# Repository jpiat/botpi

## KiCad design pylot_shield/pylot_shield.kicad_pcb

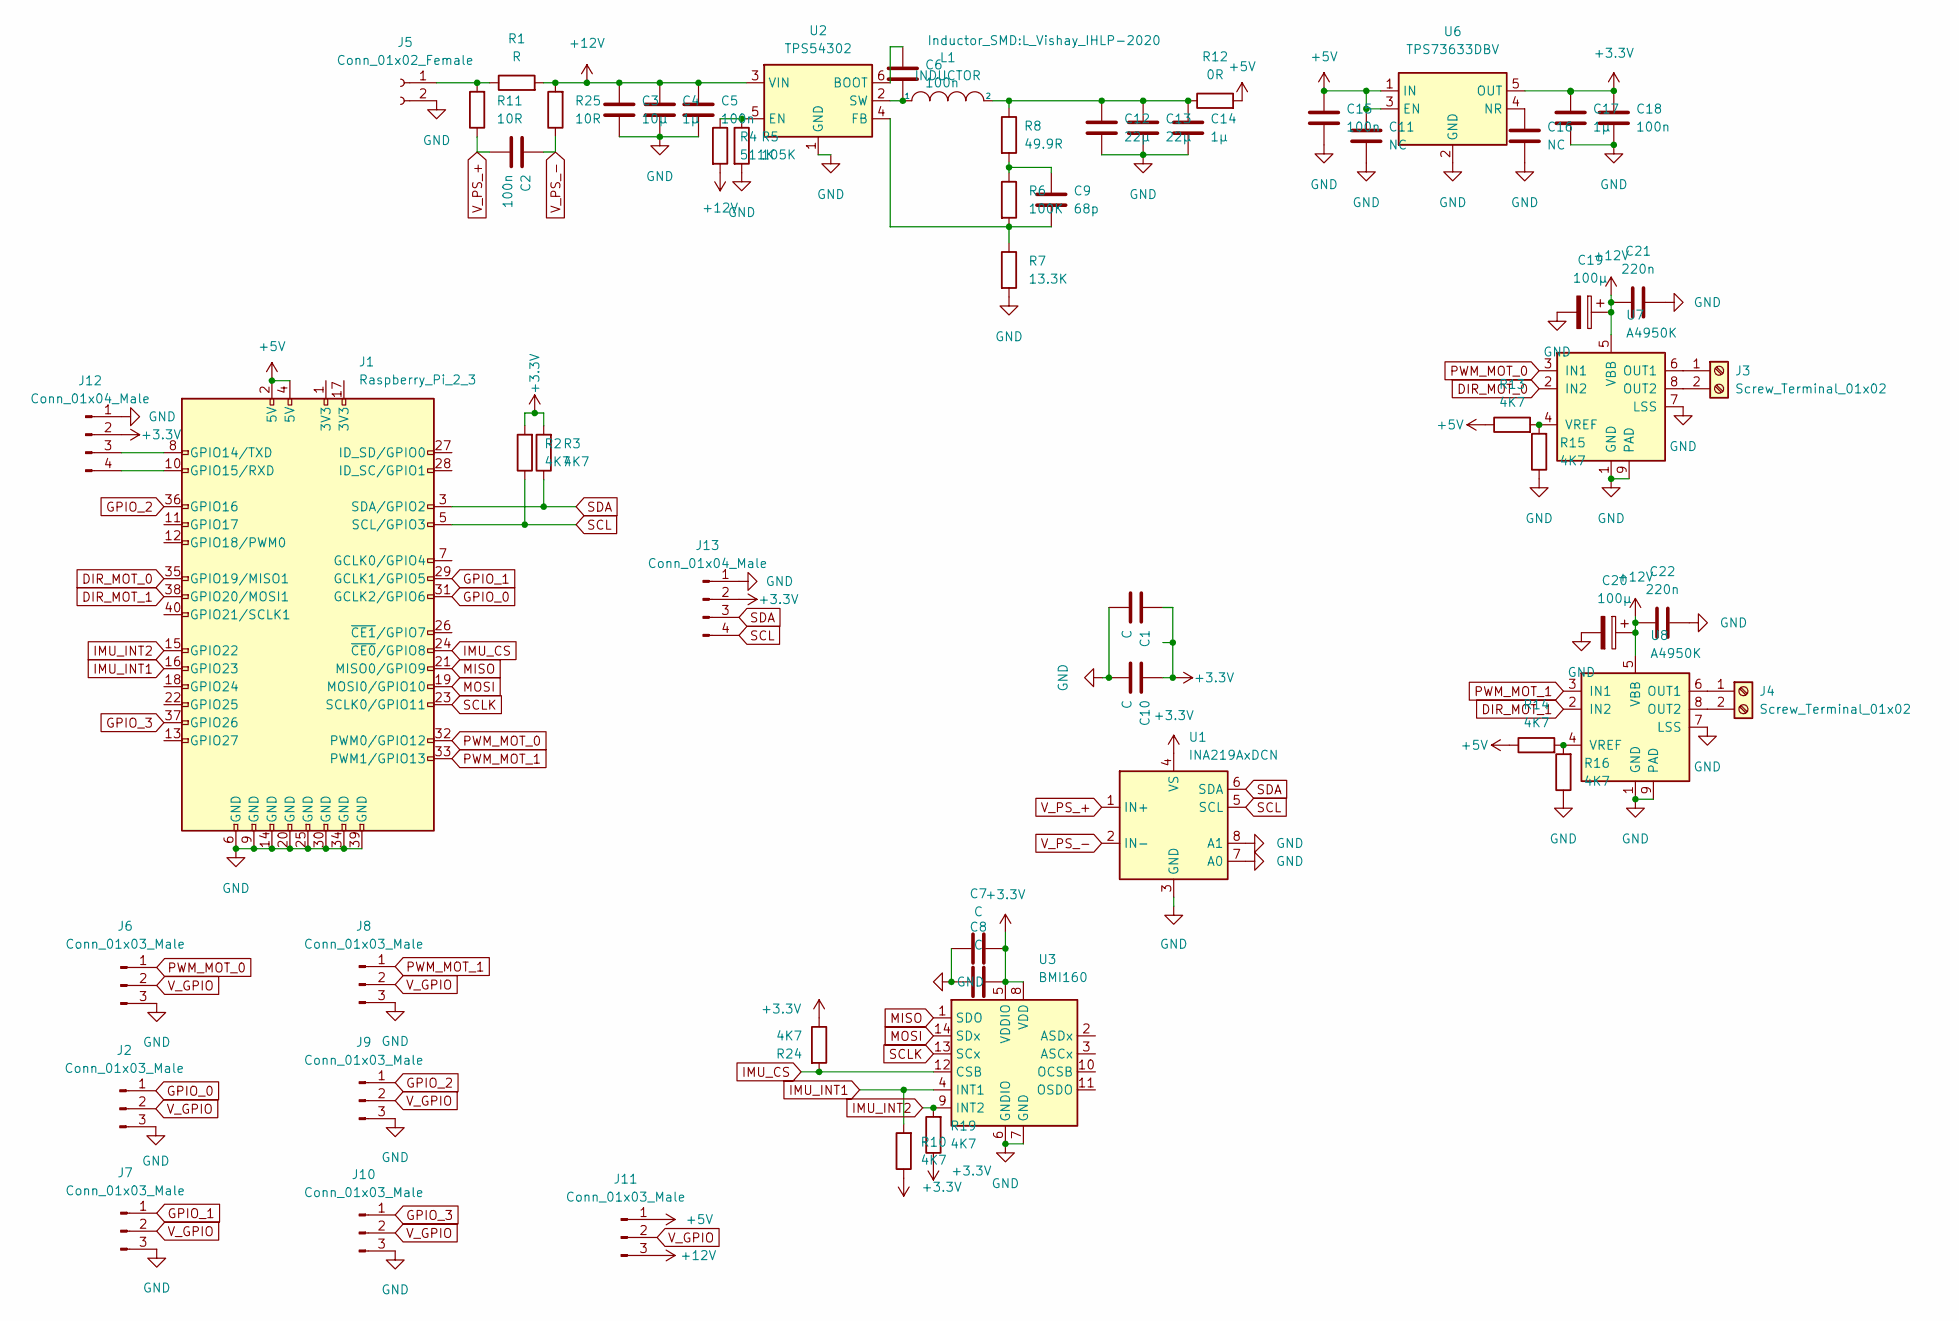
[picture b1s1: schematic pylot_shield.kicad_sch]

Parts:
C1, C7, C8, C10: C; C_0603_1608Metric
C2, C5, C6, C15, C18: 100n; C_0603_1608Metric
C3: 10µ; C_1206_3216Metric
C4: 1µ; C_1206_3216Metric
C9: 68p; C_0603_1608Metric
C11, C16: NC; C_0603_1608Metric
C12, C13: 22µ; C_1206_3216Metric
C14, C17: 1µ; C_0603_1608Metric
C19, C20: 100µ; CP_Radial_D6.3mm_P2.50mm
C21, C22: 220n; C_0603_1608Metric
J1: Raspberry_Pi_2_3; ADA3708_RPI-ZERO
J2, J6, J7, J8, J9, J10: Conn_01x03_Male; PinHeader_1x03_P2.54mm_Vertical
J3, J4: Screw_Terminal_01x02; TerminalBlock_Phoenix_PT-1,5-2-3.5-H_1x02_P3.50mm_Horizontal
J5: Conn_01x02_Female; XT30
J11: Conn_01x03_Male; SolderJumper-3_P1.3mm_Bridged2Bar12_RoundedPad1.0x1.5mm
J12, J13: Conn_01x04_Male; PinHeader_1x04_P2.00mm_Vertical
L1: INDUCTOR; L_Vishay_IHLP-2020
R1: R; R_2512_6332Metric
R2, R3, R10, R13, R14, R15, R16, R19, R24: 4K7; R_0603_1608Metric
R4: 511K; R_0603_1608Metric
R5: 105K; R_0603_1608Metric
R6: 100K; R_0603_1608Metric
R7: 13.3K; R_0603_1608Metric
R8: 49.9R; R_0603_1608Metric
R11, R25: 10R; R_0603_1608Metric
R12: 0R; R_0603_1608Metric
U1: INA219AxDCN; SOT-23-8
U2: TPS54302; SOT-23-6
U3: BMI160; Bosch_LGA-14_3x2.5mm_P0.5mm
U6: TPS73633DBV; SOT-23-5
U7, U8: A4950K; SOIC-8-1EP_3.9x4.9mm_P1.27mm_EP2.41x3.3mm

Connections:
+3.3V: C1.1, C7.2, C8.2, C10.1, C17.1, C18.1, J12.2, J13.2, R2.2, R3.2, R10.1, R19.1, R24.1, U1.4 (VS), U3.5 (VDDIO), U3.8 (VDD), U6.5 (OUT)
+5V: C11.1, C15.1, J1.2 (5V), J1.4 (5V), J11.1, R12.2, R13.1, R14.1, U6.1 (IN), U6.3 (EN)
+12V: C3.1, C4.1, C5.1, C19.1, C20.1, C21.1, C22.1, J11.3, R1.2, R4.2, R25.2, U2.3 (VIN), U7.5 (VBB), U8.5 (VBB)
DIR_MOT_0: J1.35 (GPIO19/MISO1), U7.2 (IN2)
DIR_MOT_1: J1.38 (GPIO20/MOSI1), U8.2 (IN2)
GND: C1.2, C3.2, C4.2, C5.2, C7.1, C8.1, C10.2, C11.2, C12.2, C13.2, C14.2, C15.2, C16.2, C17.2, C18.2, C19.2, C20.2, C21.2, C22.2, J1.6 (GND), J1.9 (GND), J1.14 (GND), J1.20 (GND), J1.25 (GND), J1.30 (GND), J1.34 (GND), J1.39 (GND), J2.3, J5.2, J6.3, J7.3, J8.3, J9.3, J10.3, J12.1, J13.1, R5.2, R7.2, R15.1, R16.1, U1.3 (GND), U1.7 (A0), U1.8 (A1), U2.1 (GND), U3.6 (GNDIO), U3.7 (GND), U6.2 (GND), U7.1 (GND), U7.7 (LSS), U7.9 (PAD), U8.1 (GND), U8.7 (LSS), U8.9 (PAD)
GPIO_0: J1.31 (GCLK2/GPIO6), J2.1
GPIO_1: J1.29 (GCLK1/GPIO5), J7.1
GPIO_2: J1.36 (GPIO16), J9.1
GPIO_3: J1.37 (GPIO26), J10.1
IMU_CS: J1.24 (~CE0/GPIO8), R24.2, U3.12 (CSB)
IMU_INT1: J1.16 (GPIO23), R10.2, U3.4 (INT1)
IMU_INT2: J1.15 (GPIO22), R19.2, U3.9 (INT2)
MISO: J1.21 (MISO0/GPIO9), U3.1 (SDO)
MOSI: J1.19 (MOSI0/GPIO10), U3.14 (SDx)
unnamed: C6.1, U2.6 (BOOT)
unnamed: C6.2, L1.1, U2.2 (SW)
unnamed: C9.1, R6.1, R8.2
unnamed: C9.2, R6.2, R7.1, U2.4 (FB)
unnamed: C12.1, C13.1, C14.1, L1.2, R8.1, R12.1
unnamed: C16.1, U6.4 (NR)
unnamed: J1.8 (GPIO14/TXD), J12.3
unnamed: J1.10 (GPIO15/RXD), J12.4
unnamed: J3.1, U7.6 (OUT1)
unnamed: J3.2, U7.8 (OUT2)
unnamed: J4.1, U8.6 (OUT1)
unnamed: J4.2, U8.8 (OUT2)
unnamed: J5.1, R1.1, R11.2
unnamed: R4.1, R5.1, U2.5 (EN)
unnamed: R13.2, R15.2, U7.4 (VREF)
unnamed: R14.2, R16.2, U8.4 (VREF)
PWM_MOT_0: J1.32 (PWM0/GPIO12), J6.1, U7.3 (IN1)
PWM_MOT_1: J1.33 (PWM1/GPIO13), J8.1, U8.3 (IN1)
SCL: J1.5 (SCL/GPIO3), J13.4, R2.1, U1.5 (SCL)
SCLK: J1.23 (SCLK0/GPIO11), U3.13 (SCx)
SDA: J1.3 (SDA/GPIO2), J13.3, R3.1, U1.6 (SDA)
V_GPIO: J2.2, J6.2, J7.2, J8.2, J9.2, J10.2, J11.2
V_PS_+: C2.2, R11.1, U1.1 (IN+)
V_PS_-: C2.1, R25.1, U1.2 (IN-)

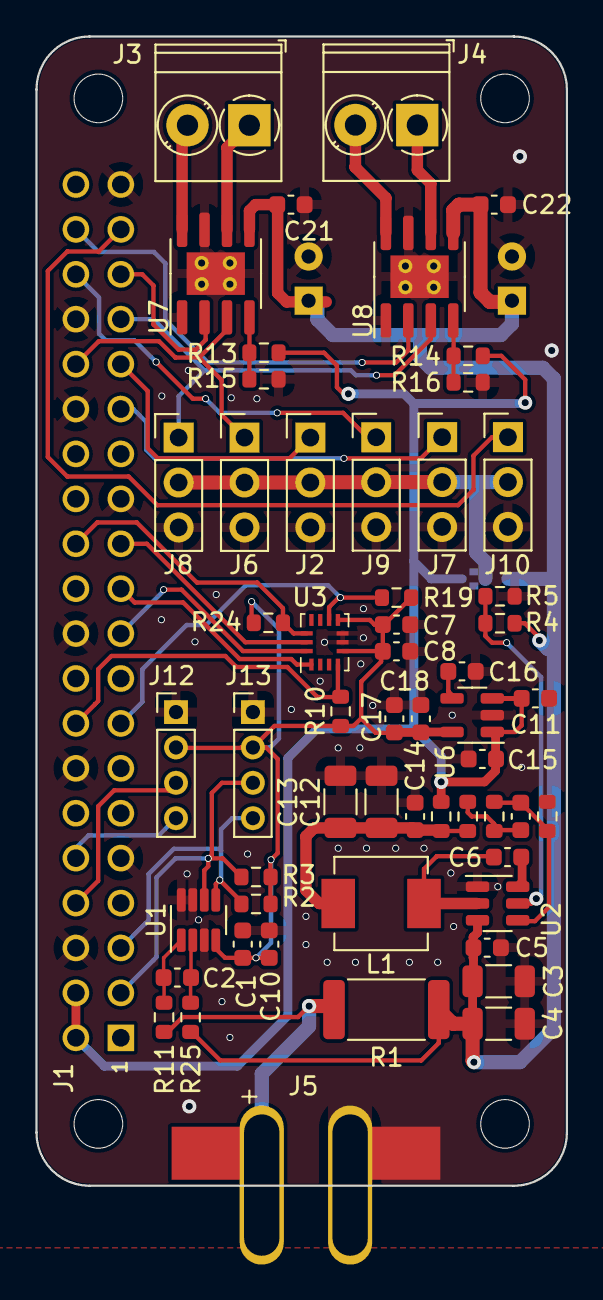
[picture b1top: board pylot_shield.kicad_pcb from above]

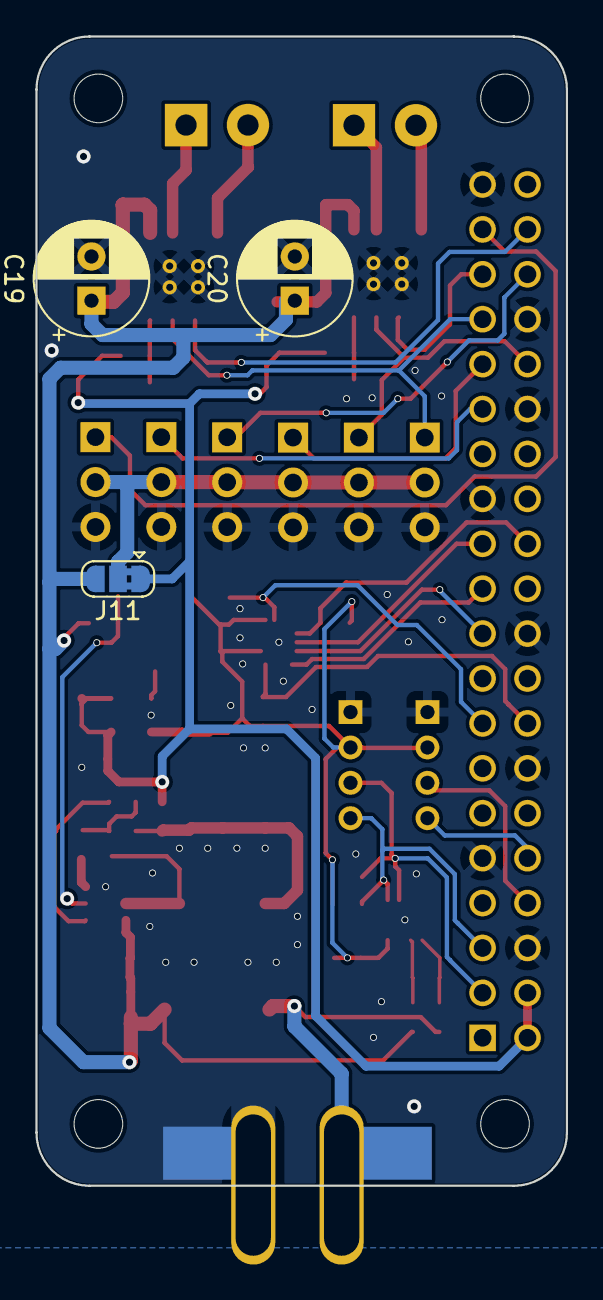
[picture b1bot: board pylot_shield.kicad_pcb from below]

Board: 2 copper layers, 30.0 x 65.0 mm, 60 parts (3 on the bottom side), 39 nets.

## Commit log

2022-10-06 Initial commit of project files
2022-10-06 Changed gitigore file
